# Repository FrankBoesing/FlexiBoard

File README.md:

# FlexiBoard

##Board for Teensy 3.2, 3.5, 3.6

https://forum.pjrc.com/threads/36869-T3-x-Flexiboard(-)

Link to board @ PCBs.io: https://pcbs.io/search?query=flexiboard
### License

<br />This work is licensed under a <a rel="license" href="http://creativecommons.org/licenses/by-sa/4.0/">Creative Commons Attribution-ShareAlike 4.0 International License</a>.

### Some Pictures

## FLASH ESP FIRMWARE

### Flash size 32Mbit: 512KB+512KB
    boot_v1.2+.bin              0x00000
    user1.1024.new.2.bin        0x01000
    esp_init_data_default.bin   0x3fc000 (optional)
    blank.bin                   0x7e000 & 0x3fe000

## Flash Firmware

1. Extract the Firmware and Flash-Tool in extras/ESP8266/Firmware.zip

2. Start ESP8266Flasher.exe and configure it :

Select the files to upload (from the zip-file):

Load FlexiBoard_FlashESP8266.ino to the Teensy

Select the COM-Port:

Reset the Teensy and click the "Flash" button

After that, you can run FlexiBoard_TalkToESP8266.ino and enter the following commands into the console to update the ESP8266-Firmware:

## Update Firmware

1.Start FlexiBoard_TalkToESP8266.ino example and select CR+LF as lineendings in the terminal.

2.Make sure the ESP is in sta or sta+ap mode

    AT+CWMODE=3
    OK

3.Make sure it got the ip address

    AT+CWJAP="YourSSID","YourWLANPassword"
    OK
    
    AT+CIFSR
    192.168.1.134

4.Let's update

    AT+CIUPDATE
    +CIPUPDATE:1    found server
    +CIPUPDATE:2    connect server
    +CIPUPDATE:3    got edition
    +CIPUPDATE:4    start start
    
    OK

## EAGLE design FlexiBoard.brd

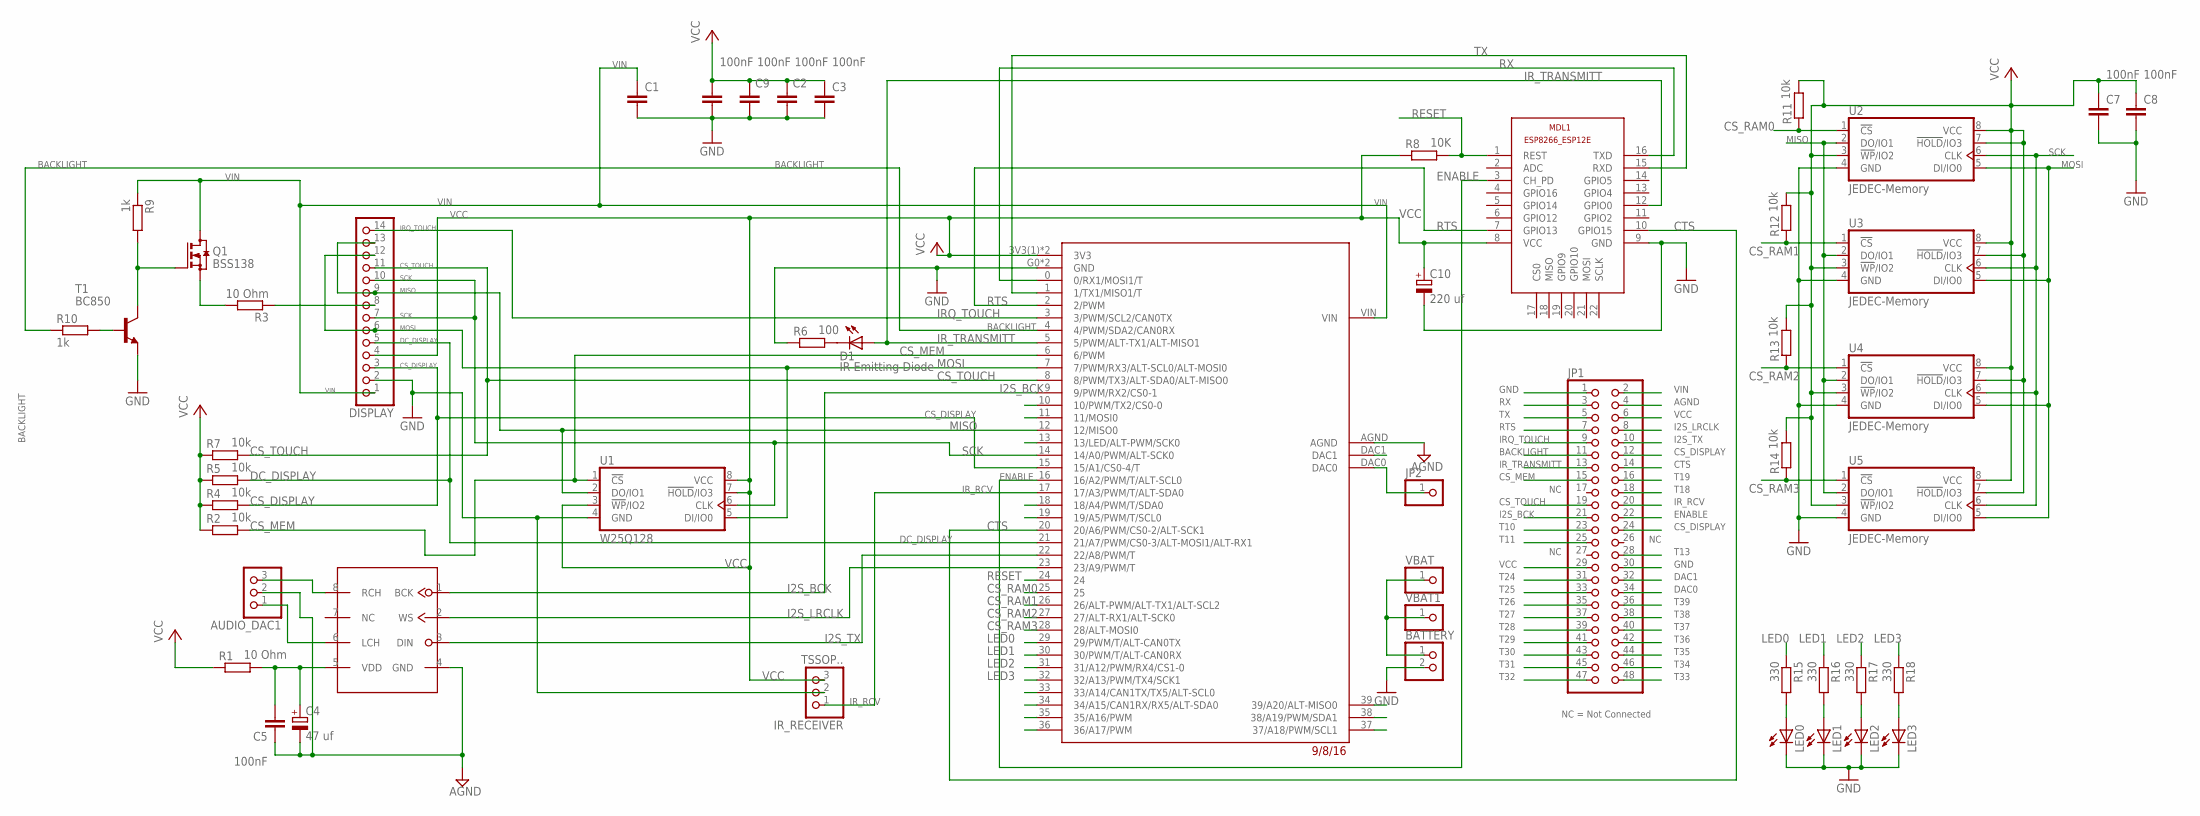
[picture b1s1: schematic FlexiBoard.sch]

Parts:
AUDIO_DAC1: PINHD-1X3/90; 1X03/90
BATTERY: PINHD-1X2; 1X02
C1, C2, C3, C5, C6, C7, C8, C9: 100nF; C0603
C4: 47 uf; E1,8-4
C10: 220 uf; E1,8-4
D1: IR Emitting Diode; SFH482
DISPLAY: PINHD-1X14; 1X14
IR_RECEIVER: TSSOP..; 1X03
JP1: PINHD-2X24; 2X24
JP2: PINHD-1X1; 1X01
LED0, LED1, LED2, LED3: LEDSML1206; SML1206
MDL1: ESP8266-12EESP8266-ESP12E; ESP8266-ESP12E
PT8211: PT8211SO8; SO8
Q1: BSS138; SOT23
R1, R3: 10 Ohm; R0603
R2, R4, R5, R7, R11, R12, R13, R14: 10k; R0603
R6: 100; R0603
R8: 10K; R0603
R9, R10: 1k; R0603
R15, R16, R17, R18: 330; R0603
T1: BC850; SOT23
U1: W25Q128; SO08-SS
U2, U3, U4, U5: JEDEC-Memory; SO08-SS
U$2: TEENSY36_OUTERPINS; T36_OUTER_PINS
VBAT, VBAT1: PINHD-1X1; 1X01

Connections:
AGND: AUDIO_DAC1.2, C4.-, C5.1, JP1.4, PT8211.4 (GND), U$2.AGND
BACKLIGHT: JP1.11, R10.1, U$2.4 (4/PWM/SDA2/CAN0RX)
CS_DISPLAY: DISPLAY.3, JP1.12, JP1.24, R4.2, U$2.15 (15/A1/CS0-4/T)
CS_MEM: JP1.15, R2.2, U1.1 (!CS!), U$2.6 (6/PWM)
CS_RAM0: R11.1, U2.1 (!CS!), U$2.25
CS_RAM1: R12.1, U3.1 (!CS!), U$2.26 (26/ALT-PWM/ALT-TX1/ALT-SCL2)
CS_RAM2: R13.1, U4.1 (!CS!), U$2.27 (27/ALT-RX1/ALT-SCK0)
CS_RAM3: R14.1, U5.1 (!CS!), U$2.28 (28/ALT-MOSI0)
CS_TOUCH: DISPLAY.11, JP1.19, R7.2, U$2.8 (8/PWM/TX3/ALT-SDA0/ALT-MISO0)
CTS: JP1.14, MDL1.10 (GPIO15), U$2.20 (20/A6/PWM/CS0-2/ALT-SCK1)
DAC0: JP1.34, JP2.1, U$2.DAC0
DAC1: JP1.32, U$2.DAC1
DC_DISPLAY: DISPLAY.5, R5.2, U$2.21 (21/A7/PWM/CS0-3/ALT-MOSI1/ALT-RX1)
ENABLE: JP1.22, MDL1.3 (CH_PD), U$2.16 (16/A2/PWM/T/ALT-SCL0)
GND: BATTERY.2, C1.2, C2.2, C3.2, C6.2, C7.2, C8.2, C9.2, C10.-, DISPLAY.2, IR_RECEIVER.2, JP1.1, JP1.30, LED0.C, LED1.C, LED2.C, LED3.C, MDL1.9 (GND), R6.1, T1.2 (E), U1.4 (GND), U2.4 (GND), U3.4 (GND), U4.4 (GND), U5.4 (GND), U$2.G0 (GND), U$2.G2 (GND)
I2S_BCK: JP1.21, PT8211.1 (BCK), U$2.9 (9/PWM/RX2/CS0-1)
I2S_LRCLK: JP1.8, PT8211.2 (WS), U$2.23 (23/A9/PWM/T)
I2S_TX: JP1.10, PT8211.3 (DIN), U$2.22 (22/A8/PWM/T)
IRQ_TOUCH: DISPLAY.14, JP1.9, U$2.3 (3/PWM/SCL2/CAN0TX)
IR_RCV: IR_RECEIVER.1, JP1.20, U$2.17 (17/A3/PWM/T/ALT-SDA0)
IR_TRANSMITT: D1.A, JP1.13, MDL1.12 (GPIO0), U$2.5 (5/PWM/ALT-TX1/ALT-MISO1)
LED0: R15.1, U$2.29 (29/PWM/T/ALT-CAN0TX)
LED1: R16.1, U$2.30 (30/PWM/T/ALT-CAN0RX)
LED2: R17.1, U$2.31 (31/A12/PWM/RX4/CS1-0)
LED3: R18.1, U$2.32 (32/A13/PWM/TX4/SCK1)
LED-DISPLAY: DISPLAY.8, R3.1
MISO: DISPLAY.9, DISPLAY.13, U1.2 (DO/IO1), U2.2 (DO/IO1), U3.2 (DO/IO1), U4.2 (DO/IO1), U5.2 (DO/IO1), U$2.12 (12/MISO0)
MOSI: DISPLAY.6, DISPLAY.12, U1.5 (DI/IO0), U2.5 (DI/IO0), U3.5 (DI/IO0), U4.5 (DI/IO0), U5.5 (DI/IO0), U$2.7 (7/PWM/RX3/ALT-SCL0/ALT-MOSI0)
unnamed: AUDIO_DAC1.1, PT8211.6 (LCH)
unnamed: Q1.2 (S), R3.2
unnamed: BATTERY.1, VBAT.1, VBAT1.1
unnamed: LED0.A, R15.2
unnamed: Q1.1 (G), R9.2, T1.3 (C)
unnamed: LED1.A, R16.2
unnamed: AUDIO_DAC1.3, PT8211.8 (RCH)
unnamed: R10.2, T1.1 (B)
unnamed: D1.K (C), R6.2
unnamed: LED2.A, R17.2
unnamed: LED3.A, R18.2
RESET: MDL1.1 (REST), R8.2, U$2.24
RTS: JP1.7, MDL1.7 (GPIO13), U$2.2 (2/PWM)
RX: JP1.3, MDL1.16 (TXD), U$2.0 (0/RX1/MOSI1/T)
SCK: DISPLAY.7, DISPLAY.10, U1.6 (CLK), U2.6 (CLK), U3.6 (CLK), U4.6 (CLK), U5.6 (CLK), U$2.14 (14/A0/PWM/ALT-SCK0)
T10: JP1.23, U$2.10 (10/PWM/TX2/CS0-0)
T11: JP1.25, U$2.11 (11/MOSI0)
T13: JP1.28, U$2.13 (13/LED/ALT-PWM/SCK0)
T18: JP1.18, U$2.18 (18/A4/PWM/T/SDA0)
T19: JP1.16, U$2.19 (19/A5/PWM/T/SCL0)
T24: JP1.31
T25: JP1.33
T26: JP1.35
T27: JP1.37
T28: JP1.39
T29: JP1.41
T30: JP1.43
T31: JP1.45
T32: JP1.47
T33: JP1.48, U$2.33 (33/A14/CAN1TX/TX5/ALT-SCL0)
T34: JP1.46, U$2.34 (34/A15/CAN1RX/RX5/ALT-SDA0)
T35: JP1.44, U$2.35 (35/A16/PWM)
T36: JP1.42, U$2.36 (36/A17/PWM)
T37: JP1.40, U$2.37 (37/A18/PWM/SCL1)
T38: JP1.38, U$2.38 (38/A19/PWM/SDA1)
T39: JP1.36, U$2.39 (39/A20/ALT-MISO0)
TX: JP1.5, MDL1.15 (RXD), U$2.1 (1/TX1/MISO1/T)
VCC: C2.1, C3.1, C6.1, C7.1, C8.1, C9.1, C10.+, DISPLAY.4, IR_RECEIVER.3, JP1.6, JP1.29, MDL1.8 (VCC), R1.1, R2.1, R4.1, R5.1, R7.1, R8.1, R11.2, R12.2, R13.2, R14.2, U1.3 (!WP!/IO2), U1.7 (!HOLD!/IO3), U1.8 (VCC), U2.3 (!WP!/IO2), U2.7 (!HOLD!/IO3), U2.8 (VCC), U3.3 (!WP!/IO2), U3.7 (!HOLD!/IO3), U3.8 (VCC), U4.3 (!WP!/IO2), U4.7 (!HOLD!/IO3), U4.8 (VCC), U5.3 (!WP!/IO2), U5.7 (!HOLD!/IO3), U5.8 (VCC), U$2.3V3(1) (3V3), U$2.3V3(3) (3V3)
VDD: C4.+, C5.2, PT8211.5 (VDD), R1.2
VIN: C1.1, DISPLAY.1, JP1.2, Q1.3 (D), R9.1, U$2.VIN

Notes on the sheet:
NC = Not Connected

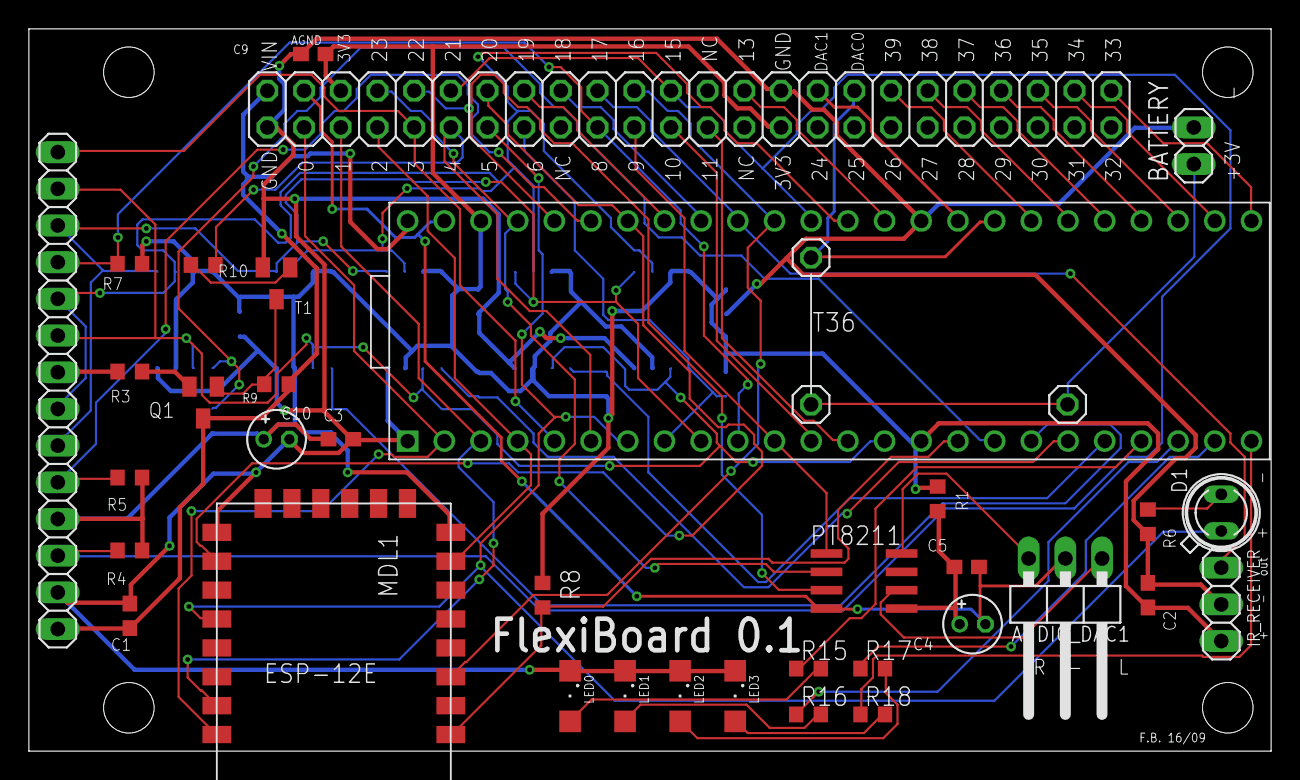
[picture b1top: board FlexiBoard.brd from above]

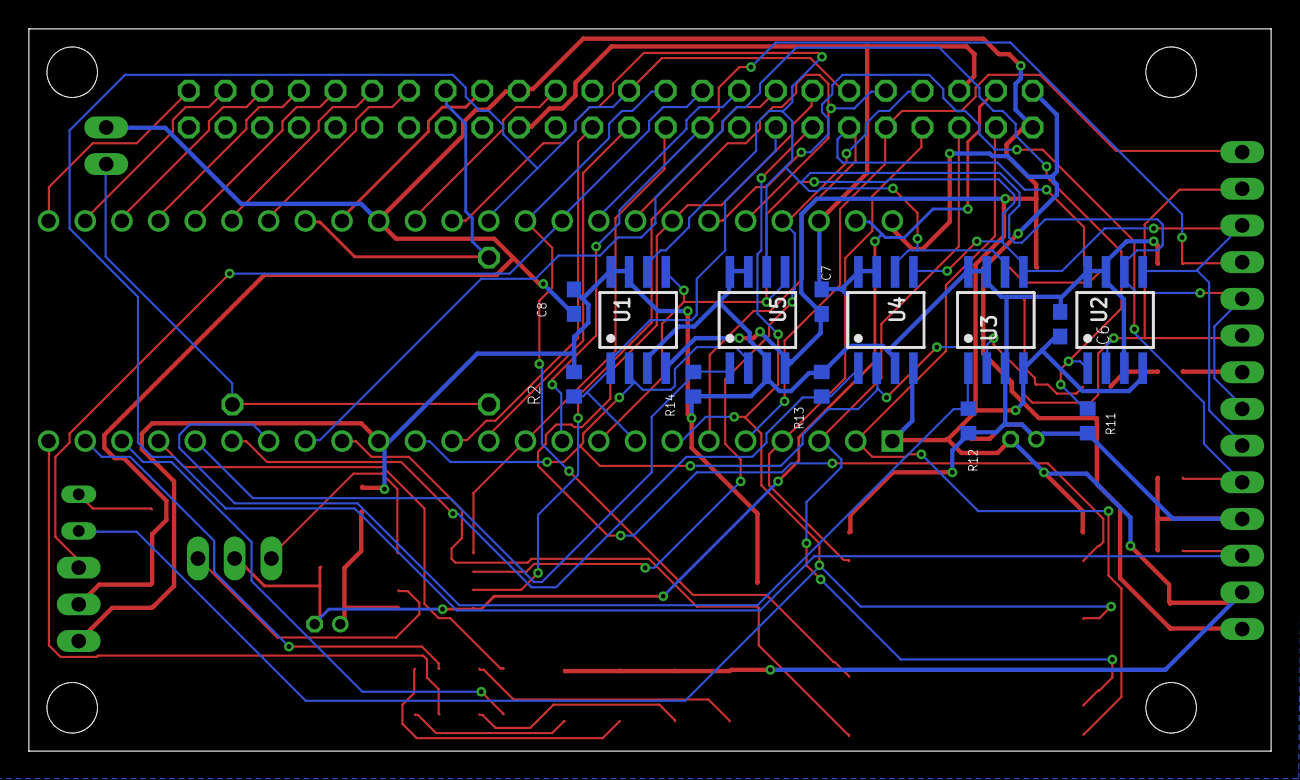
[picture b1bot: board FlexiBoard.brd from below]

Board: 2 copper layers, 86.0 x 50.0 mm, 51 parts (13 on the bottom side), 59 nets.

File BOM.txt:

Partlist

Part        Value              Device                    Package


Mount all:
C1          100nF              C-EUC0603                 C0603
C2          100nF              C-EUC0603                 C0603
C3          100nF              C-EUC0603                 C0603
C5          100nF              C-EUC0603                 C0603
C6          100nF              C-EUC0603                 C0603
C7          100nF              C-EUC0603                 C0603
C8          100nF              C-EUC0603                 C0603
C9          100nF              C-EUC0603                 C0603


WLAN
=====
ESP8266-ESP12E
C10         220 uf             CPOL-EUE1.8-4             E1,8-4
R8          10K                R-EU_R0603                R0603

AUDIO
=======
PT8211      PT8211SO8          PT8211SO8                 SO8
AUDIO_DAC1                     PINHD-1X3/90              1X03/90
C4          47 uf              CPOL-EUE1.8-4             E1,8-4
R1          10 Ohm             R-EU_R0603                R0603

MEMORY
======
For example RAM 23LC1024 or Flash W25Q128

U1          JEDEC-Memory       				 SOIC-8
U2          JEDEC-Memory
U3          JEDEC-Memory
U4          JEDEC-Memory
U5          JEDEC-Memory
R2          10k                R-EU_R0603                R0603
R11         10k                R-EU_R0603                R0603
R12         10k                R-EU_R0603                R0603
R13         10k                R-EU_R0603                R0603
R14         10k                R-EU_R0603                R0603


IR RECEIVE
==========
For example TSOP1136 or many others.
IR_RECEIVER TSOP..             PINHD-1X3                 1X03

IR SEND
==========
D1          IR Emitting Diode  ????                      ????
R6          100                R-EU_R0603                R0603

VBAT:
=====
VBAT                           PINHD-1X1                 1X01
VBAT1                          PINHD-1X1                 1X01
BATTERY                        PINHD-1X2                 1X02

LED:
======

LED0                           LEDSML1206                SML1206
LED1                           LEDSML1206                SML1206
LED2                           LEDSML1206                SML1206
LED3                           LEDSML1206                SML1206
R15         330 Ohm            R-EU_R0603                R0603
R16         330 Ohm            R-EU_R0603                R0603
R17         330 Ohm            R-EU_R0603                R0603
R18         330 Ohm            R-EU_R0603                R0603


DISPLAY
=======
ILI9341 with touch

T1          BC850              BC850                     SOT23
Q1          BSS138             BSS123                    SOT23
R3          10 Ohm             R-EU_R0603                R0603
R4          10k                R-EU_R0603                R0603

R5          10k                R-EU_R0603                R0603

R7          10k                R-EU_R0603                R0603
R9          1k                 R-EU_R0603                R0603
R10         1k                 R-EU_R0603                R0603
DISPLAY                        PINHD-1X14                1X14

JP1                            PINHD-2X24                2X24

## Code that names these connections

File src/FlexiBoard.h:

#ifndef _FlexiBoard_h_
#define _FlexiBoard_h_

/* ============================================================================================================== */
/* Edit the configuration of the FlexiBoard here:                                                                 */

#define HAVE_PT8211		1 	// 0= not available / 1=available
#define HAVE_ILI9341	1	// 0= not available / 1=available

#define HAVE_ESP12E		1	// 0= not available / 1=available
#define HAVE_RTL8710	0	// 0= not available / 1=available

#define HAVE_IR_SND	1	// 0= not available / 1=available
#define HAVE_IR_RCV	1	// 0= not available / 1=available

#define HAVE_FLASH	1	// 0= not available / 1=available	(U0 is either FLASH or RAM!)
#define HAVE_RAM0	0	// 0= not available / 1=available	(U0 is either FLASH or RAM!)
#define HAVE_RAM1	1	// 0= not available / 1=available
#define HAVE_RAM2	1	// 0= not available / 1=available
#define HAVE_RAM3	1	// 0= not available / 1=available
#define HAVE_RAM4	1	// 0= not available / 1=available
#define RAM_SIZE	(128 * 1024)	// 23LC1024 = 128KB

#define HAVE_LED0	1	// 0= not available / 1=available
#define HAVE_LED1	1	// 0= not available / 1=available
#define HAVE_LED2	1	// 0= not available / 1=available
#define HAVE_LED3	1	// 0= not available / 1=available


/* ============================================================================================================== */
/* DON'T Edit below this line                                                                                     */

#if HAVE_FLASH && HAVE_RAM0
#error FlexiBoard.h: Configuration error!!!
#endif

#define SCK  14
#define MISO 12
#define MOSI  7

#define LEDT LED_BUILTIN   //Teensy-LED

#if HAVE_LED0
#define LED0 29   //red
#else
#define LED0 255
#endif

#if HAVE_LED1
#define LED1 30   //orange
#else
#define LED1 255
#endif

#if HAVE_LED2
#define LED2 31   //green
#else
#define LED2 255
#endif

#if HAVE_LED3
#define LED3 32   //blue
#else
#define LED3 255
#endif

const uint8_t ledArr[] = { LED0, LED1, LED2, LED3 };
#define SETLED(_led,_onoff) { if ( (_led < sizeof(ledArr) ) && ledArr[_led]<255) digitalWriteFast(ledArr[_led],_onoff); }

#define TFT_BACKLIGHT   4
#define TFT_TOUCH_CS    8
#define TFT_TOUCH_INT   3
#define TFT_DC          21
#define TFT_CS          15
#define TFT_RST         255  // 255 = unused, connected to 3.3V
#define TFT_SCLK        SCK
#define TFT_MOSI        MOSI
#define TFT_MISO        MISO

#define MEM0_CS         6
#define MEM1_CS         25
#define MEM2_CS         26
#define MEM3_CS         27
#define MEM4_CS         28

uint8_t ramArrCS[] = {
#if HAVE_FLASH
#define FLASH_CS		MEM0_CS
#elif HAVE_RAM0
	MEM0_CS,
#endif
#if HAVE_RAM1
	MEM1_CS,
#endif
#if HAVE_RAM2
	MEM2_CS,
#endif
#if HAVE_RAM3
	MEM3_CS,
#endif
#if HAVE_RAM4
	MEM4_CS
#endif
	};

#define HAVE_RAM 		(defined(HAVE_RAM0) || defined(HAVE_RAM1) || defined(HAVE_RAM2) ||\
						 defined(HAVE_RAM3) || defined(HAVE_RAM4))
#define NUM_RAMS		(sizeof(ramArrCS))
#define RAM_SIZE_TOTAL	(NUM_RAMS * RAM_SIZE)


#define IR_RCV          17
#define IR_SND          5  //Shared with WLAN_GPIO0 !

#define WLAN_SERIAL     Serial1
#define WLAN_SERIAL_BAUD_INIT 74880
#define WLAN_SERIAL_BAUD 115200
#define WLAN_RESET      24
#define WLAN_ENABLE     16  //CH_PD
#define WLAN_CTS        20  //GPIO15
#define WLAN_RTS        2   //GPIO13
#define WLAN_GPIO0      5   //Shared with IR_SND !
#define WLAN_GPIO13     WLAN_RTS
#define WLAN_GPIO15     WLAN_CTS


void setBacklight(float brightness) { // ( range from 0 to 1.0 )
#if HAVE_ILI9341
  int b;

  b = 256 - roundf(256.0f * brightness);

  if (b < 0) b = 0;
  if (b > 256) b = 256;
  pinMode(TFT_BACKLIGHT, OUTPUT);
  analogWrite(TFT_BACKLIGHT, b); //(0=Max, 256=MIN)
#endif
}

bool resetWLAN() {
#if HAVE_ESP12E
  WLAN_SERIAL.begin(WLAN_SERIAL_BAUD);

  pinMode(WLAN_RESET, OUTPUT);
  pinMode(WLAN_ENABLE, OUTPUT);
  pinMode(WLAN_CTS, OUTPUT);
  pinMode(WLAN_GPIO0, OUTPUT);

  digitalWrite(WLAN_CTS, LOW);
  digitalWrite(WLAN_ENABLE, LOW);

  //Reset ESP
  digitalWrite(WLAN_RESET, LOW);
  delay(15);
  digitalWrite(WLAN_ENABLE, HIGH);
  digitalWrite(WLAN_RESET, HIGH);

  //The ESP - Bootloader waits for  HIGH on WLAN_GPIO0
  digitalWrite(WLAN_GPIO0, HIGH);

  bool ret = WLAN_SERIAL.findUntil("ready","");

  //GPIO0 ist not needed anymore:
  pinMode(WLAN_GPIO0, INPUT);

  //Disable all used pins if no response from ESP
  if (!ret) {
    pinMode(WLAN_RESET, INPUT);
    pinMode(WLAN_ENABLE, INPUT);
    pinMode(WLAN_CTS, INPUT);
  }

  return ret;
#endif
}



void initLEDs(void) {
  if (LED0<255) pinMode(LED0, OUTPUT);
  if (LED1<255) pinMode(LED1, OUTPUT);
  if (LED2<255) pinMode(LED2, OUTPUT);
  if (LED3<255) pinMode(LED3, OUTPUT);
}


void initMEM() {
#if HAVE_FLASH
 pinMode(MEM0_CS, OUTPUT); digitalWriteFast(MEM0_CS, HIGH);
#endif 
 for (unsigned i=0; i<NUM_RAMS; i++) {
	pinMode(ramArrCS[i], OUTPUT); digitalWriteFast(ramArrCS[i], HIGH);
 }
}

#endif

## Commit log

2016-10-04 Upload Files
2016-10-04 Add ESP Examples
2016-10-04 Add more pictures
2016-10-04 Update comments
2016-10-05 Testing with a placeholder.
2016-10-05 Add Library + Touchpaint Example
2016-10-05 Update Example
2016-10-05 Add Firedemo
2016-10-05 Add T3TRIS Game Demo
2016-10-05 Add License
2016-10-06 Add Automatic Reset of ESP-12
    Variants "nodemcu" and "ck"
2016-10-06 Switch off TFT-Backlight
2016-10-06 Add pictures
2016-10-07 READ ME for using ARDUINO on ESP
2016-10-07 UPDATE from PJRC Forum Post
    These are the known steps and items to run an OTA capable WEB and FTP server on your ESP.
    It will get NTP time and some other cool things I may not have found yet
2016-10-07 Placed a README2 in the ESP8266 folder
2016-10-07 OTA details update for README2 in the ESP8266 folder
2016-10-07 OTA details update for README2 in the ESP8266 folder
    formatting
2016-10-07 Start in ESP "Run" Mode
2016-10-08 First Uploads for RTL8710 WLAN
2016-10-08 Upgrade FlexiBoard.h
2016-10-15 SPI-Flash Examples
2016-10-29 Upload Eample Internetradio
2016-10-29 +add changes to Serial1.c
2016-10-29 typo
2016-10-29 Create license
2016-11-13 fix minor problem

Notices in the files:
parts and their libraries:
winbond: Copyright (C) 2010, Bob Starr
